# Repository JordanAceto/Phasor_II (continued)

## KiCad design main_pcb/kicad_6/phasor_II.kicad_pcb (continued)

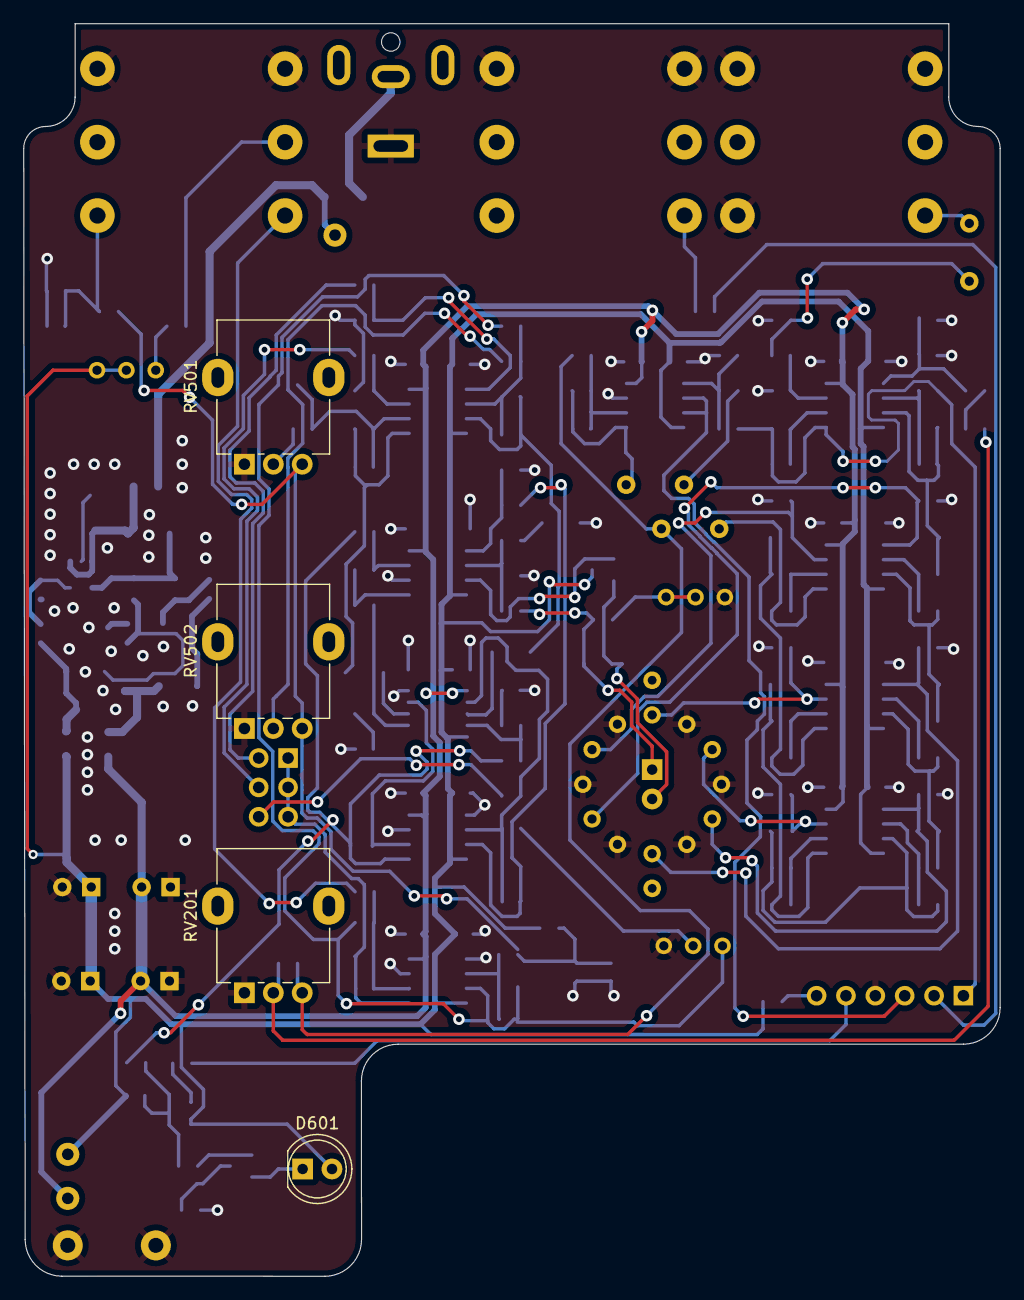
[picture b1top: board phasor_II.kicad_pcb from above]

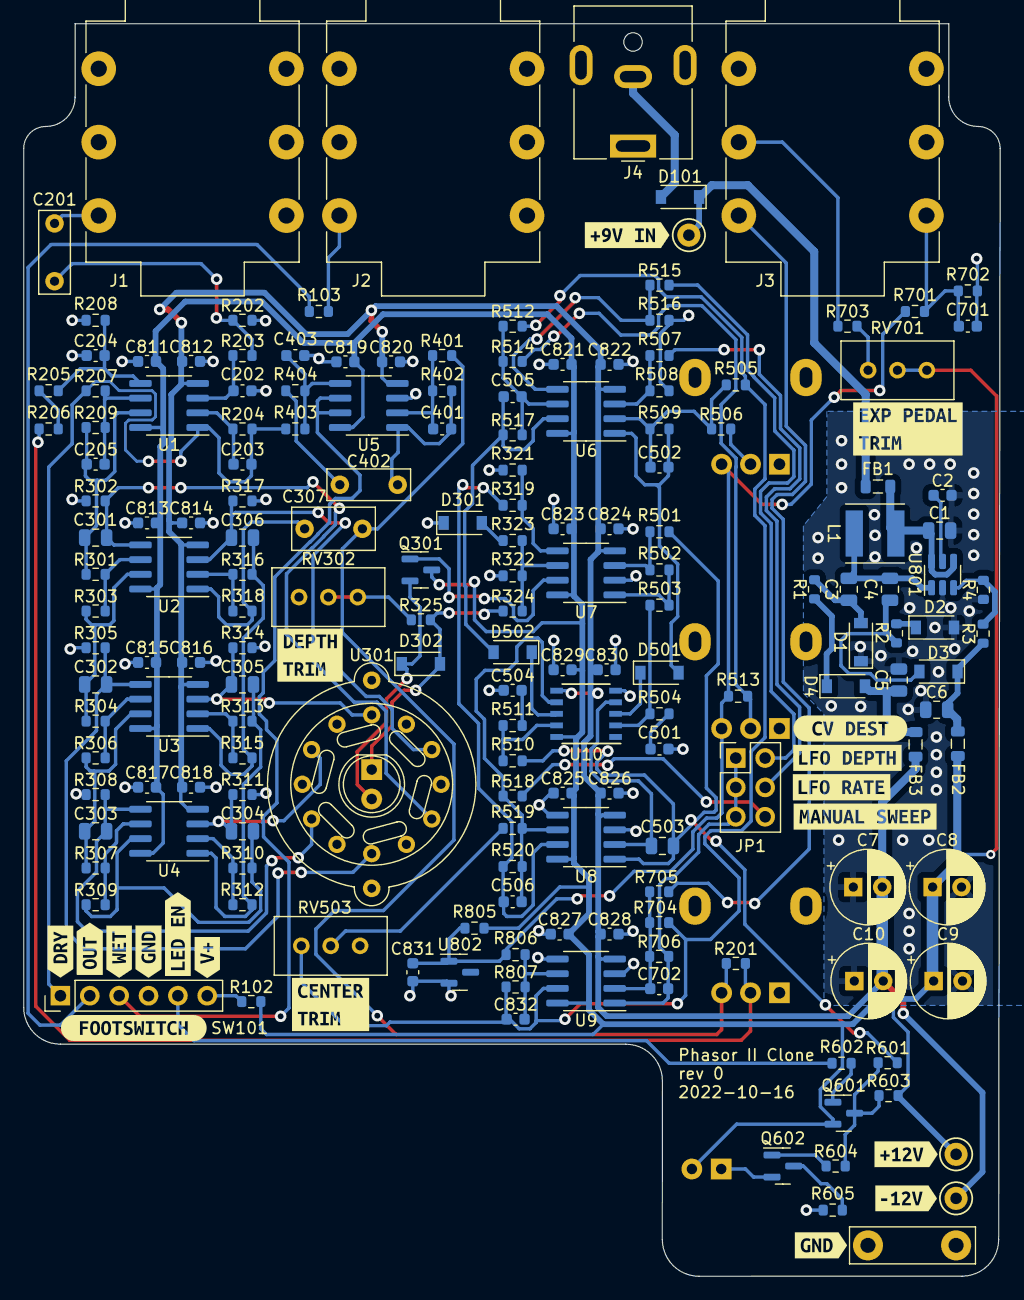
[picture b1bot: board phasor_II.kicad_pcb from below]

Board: 2 copper layers, 84.5 x 108.3 mm, 196 parts (192 on the bottom side), 98 nets.

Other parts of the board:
kibuzzard-634AF3B0: G***; kibuzzard-634AF3B0
kibuzzard-634AF3EB: G***; kibuzzard-634AF3EB
kibuzzard-634AF4C0: G***; kibuzzard-634AF4C0
kibuzzard-634AF4C9: G***; kibuzzard-634AF4C9
kibuzzard-634AF4D7: G***; kibuzzard-634AF4D7
kibuzzard-634AF45B: G***; kibuzzard-634AF45B
kibuzzard-634AF49E: G***; kibuzzard-634AF49E
kibuzzard-634AF397: G***; kibuzzard-634AF397
kibuzzard-634AF403: G***; kibuzzard-634AF403
kibuzzard-634AF413: G***; kibuzzard-634AF413
kibuzzard-634AF436: G***; kibuzzard-634AF436
kibuzzard-634AF448: G***; kibuzzard-634AF448
kibuzzard-634B0B87: G***; kibuzzard-634B0B87
kibuzzard-634B0BBC: G***; kibuzzard-634B0BBC
kibuzzard-634B0BDD: G***; kibuzzard-634B0BDD
kibuzzard-634B0C2B: G***; kibuzzard-634B0C2B
kibuzzard-634B3AE3: G***; kibuzzard-634B3AE3
kibuzzard-634B411E: G***; kibuzzard-634B411E

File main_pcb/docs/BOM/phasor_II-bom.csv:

Row,Description,Part,References,Value,Footprint,Quantity Per PCB,Status,Datasheet
1,Unpolarized capacitor,C,C202,22p,C_0603_1608Metric,1, ,~
2,Unpolarized capacitor,C,C506,100p,C_0603_1608Metric,1, ,~
3,Unpolarized capacitor,C,C403,470p,C_0603_1608Metric,1, ,~
4,Unpolarized capacitor,C,C205 C401 C501 C502 C504 C505,1n,C_0603_1608Metric,6, ,~
5,Unpolarized capacitor,C,C204,3n3,C_0603_1608Metric,1, ,~
6,Unpolarized capacitor,C,C301 C302 C303 C304 C305 C306,6n8,C_0805_2012Metric,6, ,~
7,Unpolarized capacitor,C,C201,47n,C_Rect_L7.0mm_W2.5mm_P5.00mm,1, ,~
8,Unpolarized capacitor,C,C503,47n,C_0805_2012Metric,1, ,~
9,Unpolarized capacitor,C,C2 C203 C701 C702 C811 C812 C813 C814 C815 C816 C817 C818 C819 C820 C821 C822 C823 C824 C825 C826 C827 C828 C829 C830 C831 C832,100n,C_0603_1608Metric,26, ,~
10,Unpolarized capacitor,C,C402,220n,C_Rect_L7.0mm_W2.5mm_P5.00mm,1, ,~
11,Unpolarized capacitor,C,C307,470n,C_Rect_L7.0mm_W3.5mm_P5.00mm,1, ,~
12,Unpolarized capacitor,C,C3 C4,1u,C_0805_2012Metric,2, ,~
13,Unpolarized capacitor,C,C1 C5 C6,4u7,C_0805_2012Metric,3, ,~
14,Polarized capacitor,C_Polarized,C7 C8 C9 C10,10u,CP_Radial_D6.3mm_P2.50mm,4, ,~
15,"75V 0.15A Fast Switching Diode, SOD-123",1N4148W,D301 D302,1N4148W,D_SOD-123,2, ,https://www.vishay.com/docs/85748/1n4148w.pdf
16,Schottky diode,D_Schottky,D1 D2 D3 D4 D101,B5819W,D_SOD-123,5, ,~
17,Schottky diode,D_Schottky,D501 D502,BAT48ZFILM,D_SOD-123,2, ,~
18,Light emitting diode,LED,D601,LED,LED_D5.0mm,1, ,~
19,"Ferrite bead, small symbol",FerriteBead_Small,FB1 FB2 FB3,100R @ 100MHz,L_0805_2012Metric,3, ,~
20,DC Barrel Jack,Jack-DC,J4,9VDC_IN,BarrelJack_CUI_PJ-063AH_Horizontal,1, ,~
21,"Audio Jack, 3 Poles (Stereo / TRS), Switched Poles (Normalling)",AudioJack3_Switch,J1 J2 J3,AUDIO_IN,Jack_6.35mm_Neutrik_NMJ6HCD2_Horizontal,3, ,~
22,"Generic connector, double row, 02x03, odd/even pin numbering scheme (row 1 odd numbers, row 2 even numbers), script generated (kicad-library-utils/schlib/autogen/connector/)",Conn_02x03_Odd_Even,JP1,exp_pedal_dest_jumper,PinHeader_2x03_P2.54mm_Vertical,1, ,~
23,Inductor symbol for simulation only,INDUCTOR,L1,"10uH, 1.2A",L_Taiyo-Yuden_NR-50xx,1, ,~
24,"0.2A Ic, 40V Vce, Small Signal NPN Transistor, SOT-23",MMBT3904,Q301,MMBT3904,SOT-23,1, ,https://www.onsemi.com/pub/Collateral/2N3903-D.PDF
25,"-0.2A Ic, -40V Vce, Small Signal PNP Transistor, SOT-23",MMBT3906,Q601 Q602,MMBT3906,SOT-23,2, ,https://www.onsemi.com/pub/Collateral/2N3906-D.PDF
26,Resistor,R,R1 R2,1,R_0603_1608Metric,2, ,~
27,Resistor,R,R325,220,R_0603_1608Metric,1, ,~
28,Resistor,R,R504 R511 R605,270,R_0603_1608Metric,3, ,~
29,Resistor,R,R103,1k,R_0603_1608Metric,1, ,~
30,Resistor,R,R206,1k5,R_0603_1608Metric,1, ,~
31,Resistor,R,R805,1k8,R_0603_1608Metric,1, ,~
32,Resistor,R,R203 R321,3k9,R_0603_1608Metric,2, ,~
33,Resistor,R,R201 R205 R207 R208 R209 R301 R303 R304 R306 R307 R309 R310 R312 R313 R315 R316 R318 R401 R402 R404,4k7,R_0603_1608Metric,20, ,~
34,Resistor,R,R102 R323 R513 R701 R702,10k,R_0603_1608Metric,5, ,~
35,Resistor,R,R403 R508,12k,R_0603_1608Metric,2, ,~
36,Resistor,R,R4,13k3,R_0603_1608Metric,1, ,~
37,Resistor,R,R516,18k,R_0603_1608Metric,1, ,~
38,Resistor,R,R703,20k,R_0603_1608Metric,1, ,~
39,Resistor,R,R503 R603,22k,R_0603_1608Metric,2, ,~
40,Resistor,R,R509,30k,R_0603_1608Metric,1, ,~
41,Resistor,R,R601,33k,R_0603_1608Metric,1, ,~
42,Resistor,R,R519,39k,R_0603_1608Metric,1, ,~
43,Resistor,R,R505 R517,56k,R_0603_1608Metric,2, ,~
44,Resistor,R,R319 R322,68k,R_0603_1608Metric,2, ,~
45,Resistor,R,R501 R507 R510 R515 R518 R520 R602 R604 R705 R806 R807,100k,R_0603_1608Metric,11, ,~
46,Resistor,R,R506,110k,R_0603_1608Metric,1, ,~
47,Resistor,R,R3,114k,R_0603_1608Metric,1, ,~
48,Resistor,R,R512 R514,120k,R_0603_1608Metric,2, ,~
49,Resistor,R,R704 R706,200k,R_0603_1608Metric,2, ,~
50,Resistor,R,R302 R305 R308 R311 R314 R317 R324 R502,220k,R_0603_1608Metric,8, ,~
51,Resistor,R,R202 R204,390k,R_0603_1608Metric,2, ,~
52,Trim-potentiometer,R_Potentiometer_Trim,RV302,1k,Potentiometer_Bourns_3296W_Vertical,1, ,~
53,Potentiometer,R_Potentiometer,RV201,10k,Potentiometer_Alpha_RD901F-40-00D_Single_Vertical,1, ,~
54,Potentiometer,R_Potentiometer,RV501 RV502,100k,Potentiometer_Alpha_RD901F-40-00D_Single_Vertical,2, ,~
55,Trim-potentiometer,R_Potentiometer_Trim,RV503 RV701,100k,Potentiometer_Bourns_3296W_Vertical,2, ,~
56,"Momentary Switch, dual pole double throw",SW_Push_DPDT,SW101,FOOTSWITCH,PinHeader_1x06_P2.54mm_Vertical,1, ,~
57,,LDR_ring,U301,LDR_ring,LDR_ring,1, ,
58,"5.000V Precision Micropower Shunt Voltage Reference, SOT-23",LM4040DBZ-5,U802,LM4040DBZ-5,SOT-23,1, ,http://www.ti.com/lit/ds/symlink/lm4040-n.pdf
59,,LT3467A,U801,LT3467A,TSOT-23-6,1, ,
60,"Dual General Purpose, Operational Amplifier, DIP-8/SOIC-8/SSOP-8",RC4558,U1 U2 U3 U4 U5,RC4558,SOIC-8_3.9x4.9mm_P1.27mm,5, ,http://www.ti.com/lit/ds/symlink/rc4558.pdf
61,,SSI2162,U10,SSI2162,SSOP-10_3.9x4.9mm_P1.00mm,1, ,https://www.soundsemiconductor.com/downloads/ssi2162datasheet.pdf
62,"Dual Low-Noise JFET-Input Operational Amplifiers, DIP-8/SOIC-8",TL072,U6 U7 U8 U9,TL072,SOIC-8_3.9x4.9mm_P1.27mm,4, ,http://www.ti.com/lit/ds/symlink/tl071.pdf





Project info:
Schematic:,phasor_II
Variant:,default
Revision:,0
Date:,2022-10-15
KiCad Version:,6.0.5+dfsg-1~bpo11+1
Statistics:
Component Groups:,62
Component Count:,174 (143 SMD/ 20 THT)
Fitted Components:,174 (143 SMD/ 20 THT)
Number of PCBs:,1
Total Components:,174

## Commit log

2023-01-30 Add notes about pcb panel thickness
2023-01-30 Add licence
2023-01-30 Update README with checkboxes after successful build
2023-01-31 Add images, update README
2023-02-01 Fix CV range notes in schem, add note about tapering R
2023-02-01 Add gitignore
2023-02-01 Add link to schematic to main readme
